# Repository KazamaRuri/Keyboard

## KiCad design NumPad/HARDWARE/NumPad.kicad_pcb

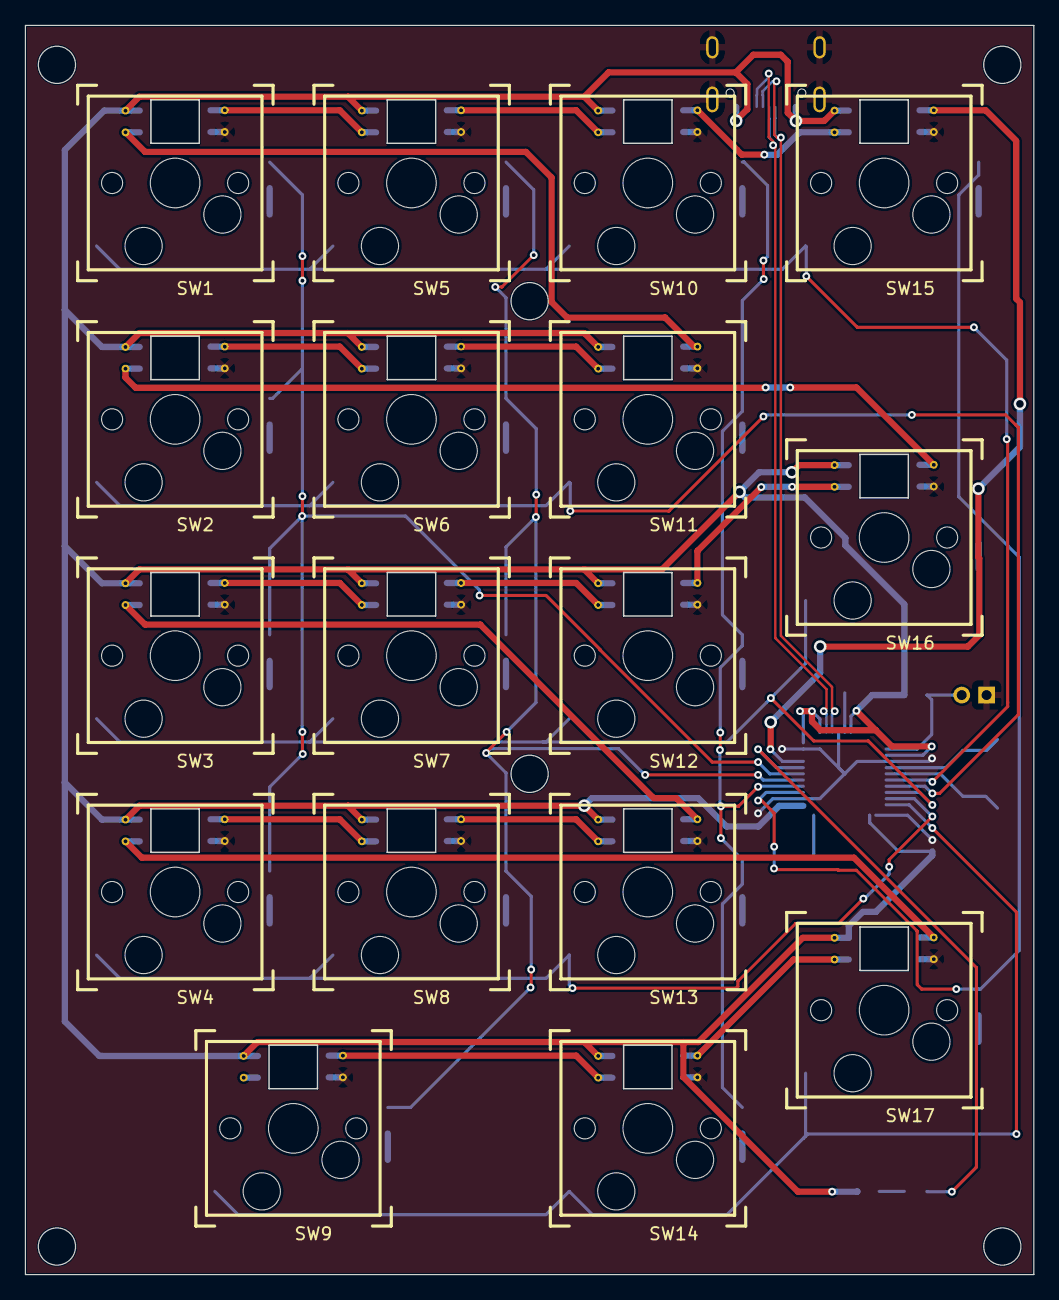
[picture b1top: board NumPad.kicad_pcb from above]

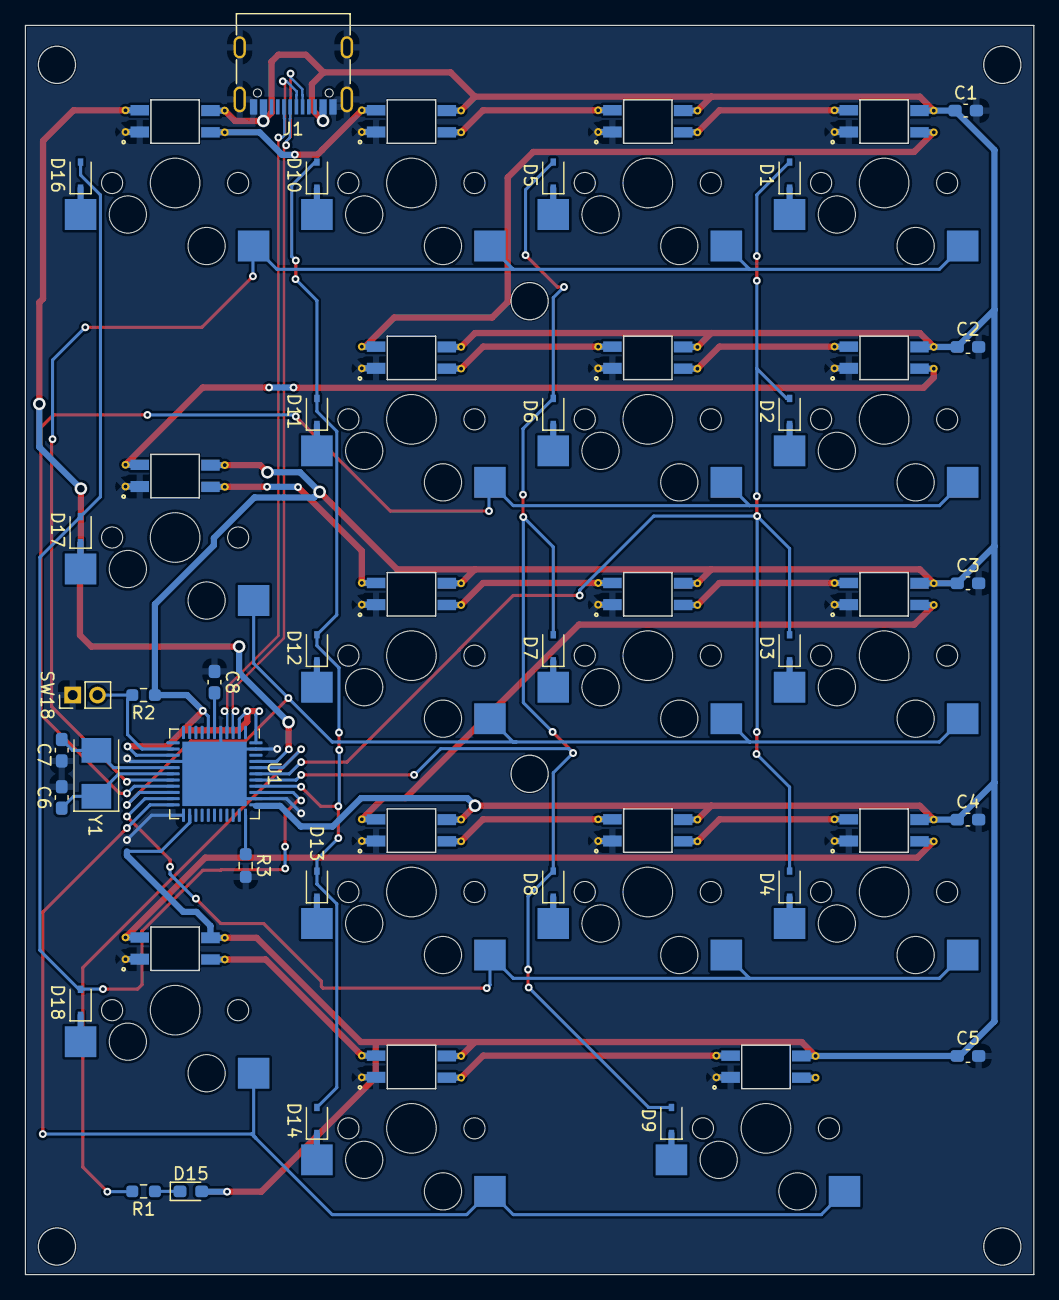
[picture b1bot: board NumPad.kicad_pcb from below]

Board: 2 copper layers, 81.3 x 100.7 mm, 50 parts (33 on the bottom side), 54 nets.

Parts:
C1, C2, C3, C4, C5: 100nF; C_0603_1608Metric_Pad1.08x0.95mm_HandSolder
C6, C7: 22pF; C_0603_1608Metric_Pad1.08x0.95mm_HandSolder
C8: 1uF; C_0603_1608Metric_Pad1.08x0.95mm_HandSolder
D1, D2, D3, D4, D5, D6, D7, D8, D9, D10, D11, D12, D13, D14, D16, D17, D18: 1N4148WS; D_SOD-323
D15: LED; LED_0603_1608Metric_Pad1.05x0.95mm_HandSolder
J1: USB; USB_C_Receptacle_G-Switch_GT-USB-7010ASV
R1, R2, R3: 10K; R_0603_1608Metric_Pad0.98x0.95mm_HandSolder
SW1, SW2, SW3, SW4, SW5, SW6, SW7, SW8, SW9, SW10, SW11, SW12, SW13, SW14, SW15, SW16, SW17: Key_WS2812
SW18: SW_Push; PinHeader_1x02_P2.00mm_Vertical
U1: ATmega32U4; QFN-44-1EP_7x7mm_P0.5mm_EP5.2x5.2mm
Y1: 16MHz; Crystal_SMD_5032-2Pin_5.0x3.2mm

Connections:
+5V: C1.1, C2.1, C3.1, C4.1, C5.1, D15.2 (A), J1.A4 (VBUS), J1.A9 (VBUS), J1.B4 (VBUS), J1.B9 (VBUS), R2.1, SW1.VDD, SW2.VDD, SW3.VDD, SW4.VDD, SW5.VDD, SW6.VDD, SW7.VDD, SW8.VDD, SW9.VDD, SW10.VDD, SW11.VDD, SW12.VDD, SW13.VDD, SW14.VDD, SW15.VDD, SW16.VDD, SW17.VDD, U1.2 (UVCC), U1.7 (VBUS), U1.14 (VCC), U1.24 (AVCC), U1.34 (VCC), U1.44 (AVCC)
/COL0: D1.2 (A), D2.2 (A), D3.2 (A), D4.2 (A), U1.39 (PF4)
/COL1: D5.2 (A), D6.2 (A), D7.2 (A), D8.2 (A), D9.2 (A), U1.38 (PF5)
/COL2: D10.2 (A), D11.2 (A), D12.2 (A), D13.2 (A), D14.2 (A), U1.37 (PF6)
/COL3: D16.2 (A), D17.2 (A), D18.2 (A), U1.36 (PF7)
/D+: J1.A6 (D+), J1.B6 (D+), U1.4 (D+)
/D-: J1.A7 (D-), J1.B7 (D-), U1.3 (D-)
/NUMLOCK: R1.2, U1.40 (PF1)
/RESET: R2.2, SW18.2, U1.13 (~RESET)
/RGB: SW15.DIN, U1.41 (PF0)
/ROW0: SW1.ROW, SW5.ROW, SW10.ROW, SW15.ROW, U1.18 (PD0)
/ROW1: SW2.ROW, SW6.ROW, SW11.ROW, U1.19 (PD1)
/ROW2: SW3.ROW, SW7.ROW, SW12.ROW, SW16.ROW, U1.20 (PD2)
/ROW3: SW4.ROW, SW8.ROW, SW13.ROW, U1.21 (PD3)
/ROW4: SW9.ROW, SW14.ROW, SW17.ROW, U1.22 (PD5)
GND: C1.2, C2.2, C3.2, C4.2, C5.2, C6.2, C7.2, C8.1, J1.A1 (GND), J1.A12 (GND), J1.B1 (GND), J1.B12 (GND), J1.S1 (SHIELD), R3.2, SW1.GND, SW2.GND, SW3.GND, SW4.GND, SW5.GND, SW6.GND, SW7.GND, SW8.GND, SW9.GND, SW10.GND, SW11.GND, SW12.GND, SW13.GND, SW14.GND, SW15.GND, SW16.GND, SW17.GND, SW18.1, U1.5 (UGND), U1.15 (GND), U1.23 (GND), U1.35 (GND), U1.43 (GND), U1.45 (GND)
unnamed: C6.1, U1.17 (XTAL1), Y1.1
unnamed: C7.1, U1.16 (XTAL2), Y1.2
unnamed: C8.2, U1.6 (UCAP)
unnamed: D1.1 (K), SW1.COL
unnamed: D2.1 (K), SW2.COL
unnamed: D3.1 (K), SW3.COL
unnamed: D4.1 (K), SW4.COL
unnamed: D5.1 (K), SW5.COL
unnamed: D6.1 (K), SW6.COL
unnamed: D7.1 (K), SW7.COL
unnamed: D8.1 (K), SW8.COL
unnamed: D9.1 (K), SW9.COL
unnamed: D10.1 (K), SW10.COL
unnamed: D11.1 (K), SW11.COL
unnamed: D12.1 (K), SW12.COL
unnamed: D13.1 (K), SW13.COL
unnamed: D14.1 (K), SW14.COL
unnamed: D15.1 (K), R1.1
unnamed: D16.1 (K), SW15.COL
unnamed: D17.1 (K), SW16.COL
unnamed: D18.1 (K), SW17.COL
unnamed: R3.1, U1.33 (~HWB/PE2)
unnamed: SW1.DIN, SW5.DOUT
unnamed: SW1.DOUT, SW11.DIN
unnamed: SW2.DIN, SW6.DOUT
unnamed: SW3.DIN, SW7.DOUT
unnamed: SW4.DIN, SW8.DOUT
unnamed: SW10.DIN, SW15.DOUT
unnamed: SW5.DIN, SW10.DOUT
unnamed: SW6.DIN, SW11.DOUT
unnamed: SW12.DIN, SW16.DOUT
unnamed: SW7.DIN, SW12.DOUT
unnamed: SW3.DOUT, SW13.DIN
unnamed: SW8.DIN, SW13.DOUT
unnamed: SW14.DIN, SW17.DOUT
unnamed: SW9.DIN, SW14.DOUT
unnamed: SW2.DOUT, SW16.DIN
unnamed: SW4.DOUT, SW17.DIN
